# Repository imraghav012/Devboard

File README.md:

# Devboard
Custom development board made for Week 5 of Half-Life.
Made in KiCad, it uses a Raspberry Pi RP2040 on a PCB to control the other components, which can be found in this repository's Bill of Materials (BOM).
It has a USB Type-C port to supply power to and flash the board. It also includes an LDO to control voltage, a X322512MSB4SI crystal oscillator to count time, and USON-8 flash storage.
Tutorial by Kai Pereira: https://blueprint.hackclub.com/starter-projects/devboard, https://github.com/KaiPereira/build-a-devboard/tree/master

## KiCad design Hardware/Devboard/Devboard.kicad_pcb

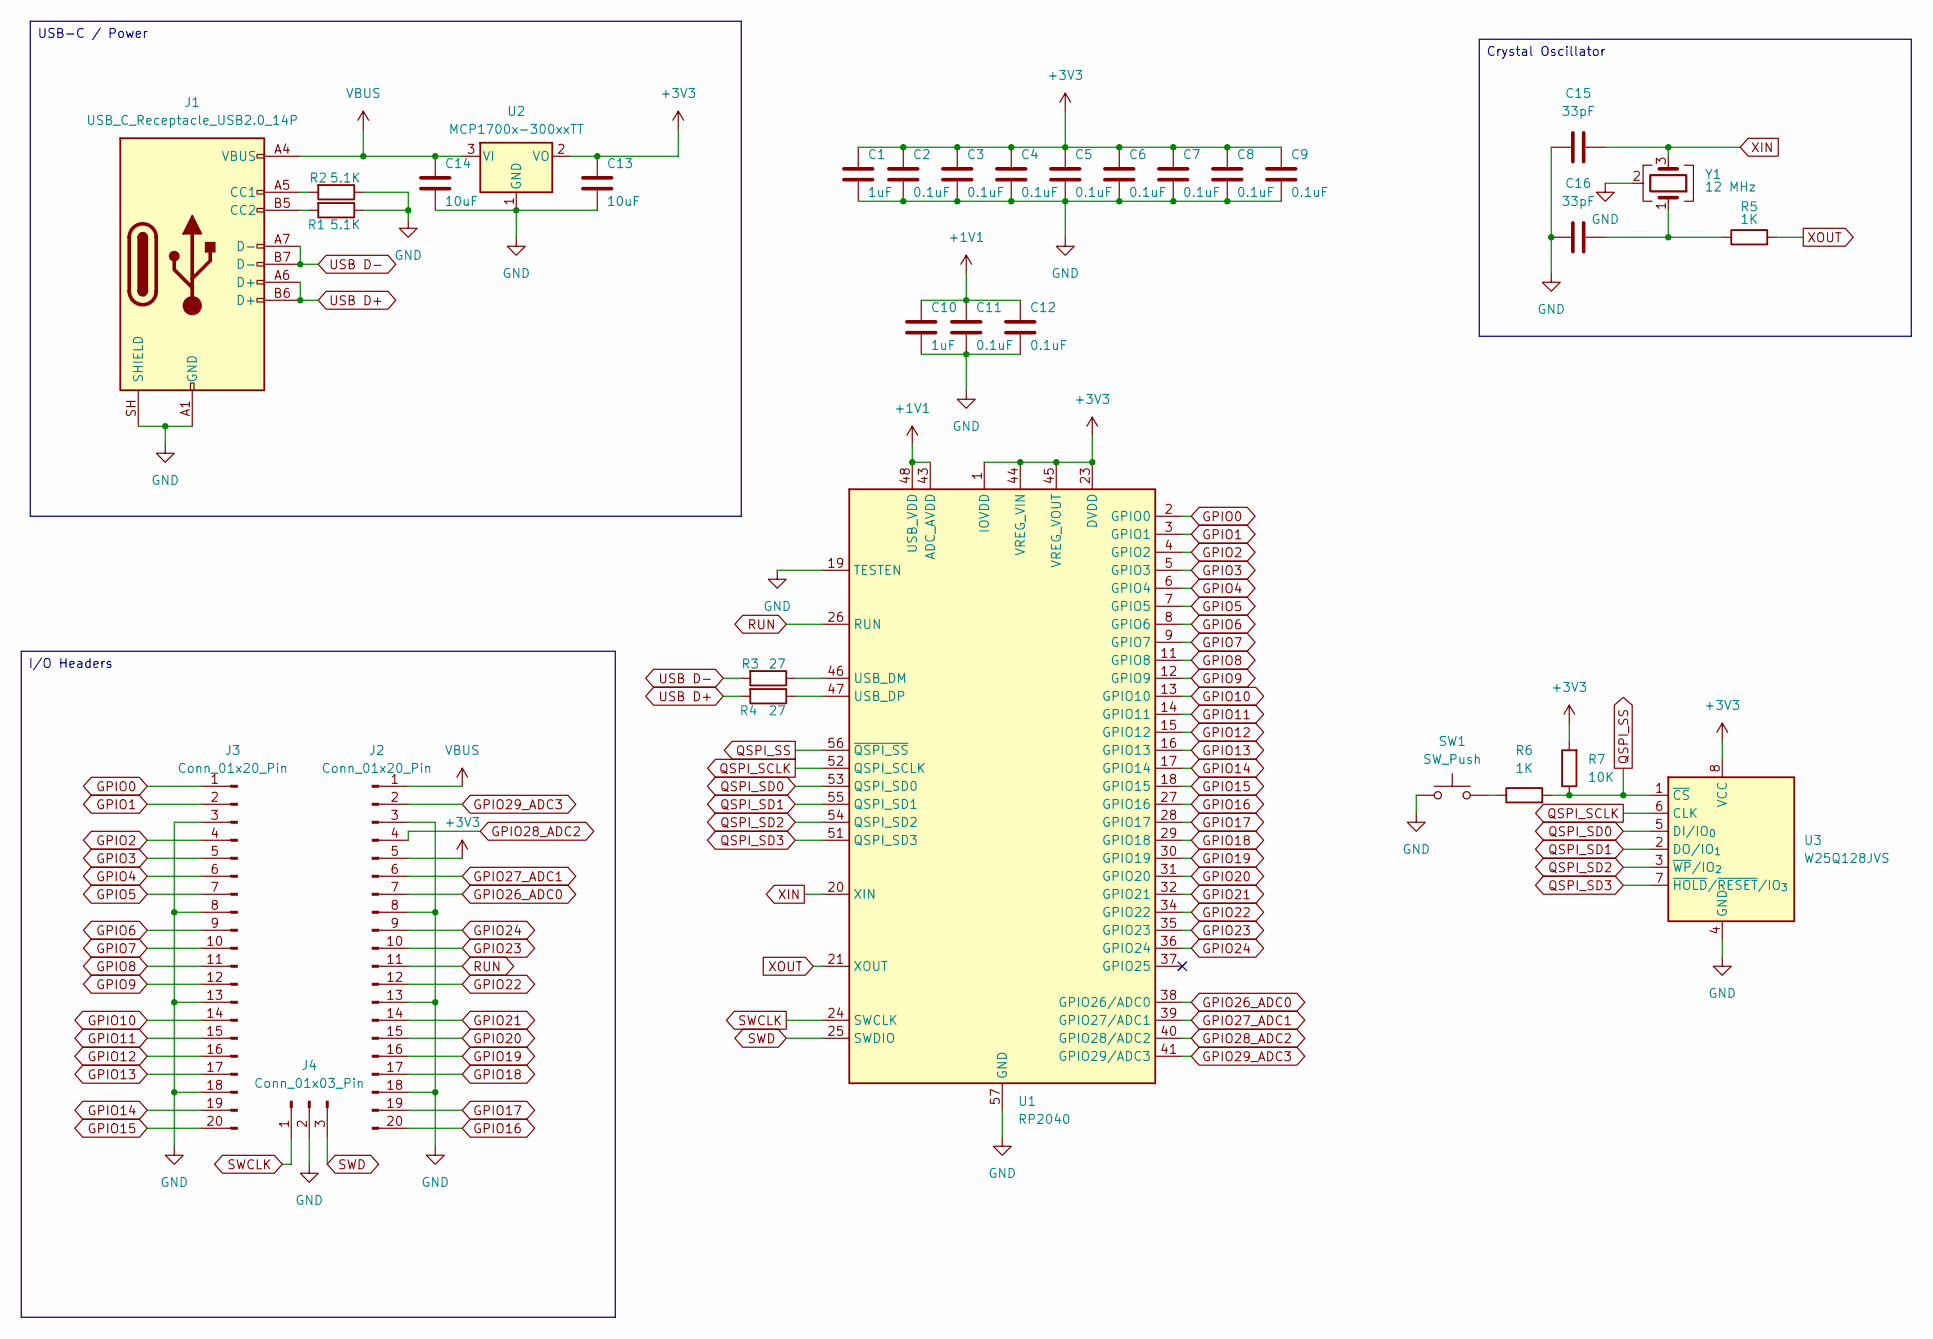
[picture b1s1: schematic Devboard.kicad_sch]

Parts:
C1, C10: 1uF; C_0402_1005Metric
C2, C3, C4, C5, C6, C7, C8, C9, C11, C12: 0.1uF; C_0402_1005Metric
C13, C14: 10uF; C_0603_1608Metric
C15, C16: 33pF; C_0402_1005Metric
J1: USB_C_Receptacle_USB2.0_14P; USB_C_Receptacle_HRO_TYPE-C-31-M-12
J2, J3: Conn_01x20_Pin; PinHeader_1x20_P2.54mm_Vertical
J4: Conn_01x03_Pin; PinHeader_1x03_P2.54mm_Vertical
R1, R2: 5.1K; R_0402_1005Metric
R3, R4: 27; R_0402_1005Metric
R5, R6: 1K; R_0402_1005Metric
R7: 10K; R_0402_1005Metric
SW1: SW_Push; SW_Push_SPST_NO_Alps_SKRK
U1: RP2040; QFN-56-1EP_7x7mm_P0.4mm_EP3.2x3.2mm
U2: MCP1700x-300xxTT; SOT-23
U3: W25Q128JVS; Winbond_USON-8-1EP_3x2mm_P0.5mm_EP0.2x1.6mm
Y1: 12 MHz; Crystal_SMD_3225-4Pin_3.2x2.5mm

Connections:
+1V1: C10.1, C11.1, C12.1, U1.43 (ADC_AVDD), U1.48 (USB_VDD)
+3V3: C1.1, C2.1, C3.1, C4.1, C5.1, C6.1, C7.1, C8.1, C9.1, C13.1, J2.5, R7.2, U1.1 (IOVDD), U1.10 (IOVDD), U1.22 (IOVDD), U1.23 (DVDD), U1.33 (IOVDD), U1.42 (IOVDD), U1.44 (VREG_VIN), U1.45 (VREG_VOUT), U1.49 (IOVDD), U1.50 (DVDD), U2.2 (VO), U3.8 (VCC)
GND: C1.2, C2.2, C3.2, C4.2, C5.2, C6.2, C7.2, C8.2, C9.2, C10.2, C11.2, C12.2, C13.2, C14.2, C15.1, C16.1, J1.A1 (GND), J1.A12 (GND), J1.B1 (GND), J1.B12 (GND), J1.SH (SHIELD), J2.3, J2.8, J2.13, J2.18, J3.3, J3.8, J3.13, J3.18, J4.2, R1.1, R2.1, SW1.1, U1.19 (TESTEN), U1.57 (GND), U2.1 (GND), U3.4 (GND), Y1.2 (G), Y1.4 (G)
GPIO0: J3.1, U1.2 (GPIO0)
GPIO1: J3.2, U1.3 (GPIO1)
GPIO2: J3.4, U1.4 (GPIO2)
GPIO3: J3.5, U1.5 (GPIO3)
GPIO4: J3.6, U1.6 (GPIO4)
GPIO5: J3.7, U1.7 (GPIO5)
GPIO6: J3.9, U1.8 (GPIO6)
GPIO7: J3.10, U1.9 (GPIO7)
GPIO8: J3.11, U1.11 (GPIO8)
GPIO9: J3.12, U1.12 (GPIO9)
GPIO10: J3.14, U1.13 (GPIO10)
GPIO11: J3.15, U1.14 (GPIO11)
GPIO12: J3.16, U1.15 (GPIO12)
GPIO13: J3.17, U1.16 (GPIO13)
GPIO14: J3.19, U1.17 (GPIO14)
GPIO15: J3.20, U1.18 (GPIO15)
GPIO16: J2.20, U1.27 (GPIO16)
GPIO17: J2.19, U1.28 (GPIO17)
GPIO18: J2.17, U1.29 (GPIO18)
GPIO19: J2.16, U1.30 (GPIO19)
GPIO20: J2.15, U1.31 (GPIO20)
GPIO21: J2.14, U1.32 (GPIO21)
GPIO22: J2.12, U1.34 (GPIO22)
GPIO23: J2.10, U1.35 (GPIO23)
GPIO24: J2.9, U1.36 (GPIO24)
GPIO26_ADC0: J2.7, U1.38 (GPIO26/ADC0)
GPIO27_ADC1: J2.6, U1.39 (GPIO27/ADC1)
GPIO28_ADC2: J2.4, U1.40 (GPIO28/ADC2)
GPIO29_ADC3: J2.2, U1.41 (GPIO29/ADC3)
unnamed: C16.2, R5.1, Y1.1
unnamed: J1.A5 (CC1), R2.2
unnamed: J1.B5 (CC2), R1.2
unnamed: R6.1, SW1.2
unnamed: R3.1, U1.46 (USB_DM)
unnamed: R4.1, U1.47 (USB_DP)
QSPI_SCLK: U1.52 (QSPI_SCLK), U3.6 (CLK)
QSPI_SD0: U1.53 (QSPI_SD0), U3.5 (DI/IO_{0})
QSPI_SD1: U1.55 (QSPI_SD1), U3.2 (DO/IO_{1})
QSPI_SD2: U1.54 (QSPI_SD2), U3.3 (~WP/IO_{2})
QSPI_SD3: U1.51 (QSPI_SD3), U3.7 (~HOLD/~RESET/IO_{3})
QSPI_SS: R6.2, R7.1, U1.56 (~QSPI_SS), U3.1 (~CS)
RUN: J2.11, U1.26 (RUN)
SWCLK: J4.1, U1.24 (SWCLK)
SWD: J4.3, U1.25 (SWDIO)
USB D+: J1.A6 (D+), J1.B6 (D+), R4.2
USB D-: J1.A7 (D-), J1.B7 (D-), R3.2
VBUS: C14.1, J1.A4 (VBUS), J1.A9 (VBUS), J1.B4 (VBUS), J1.B9 (VBUS), J2.1, U2.3 (VI)
XIN: C15.2, U1.20 (XIN), Y1.3
XOUT: R5.2, U1.21 (XOUT)

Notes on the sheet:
I/O Headers
Crystal Oscillator
USB-C / Power

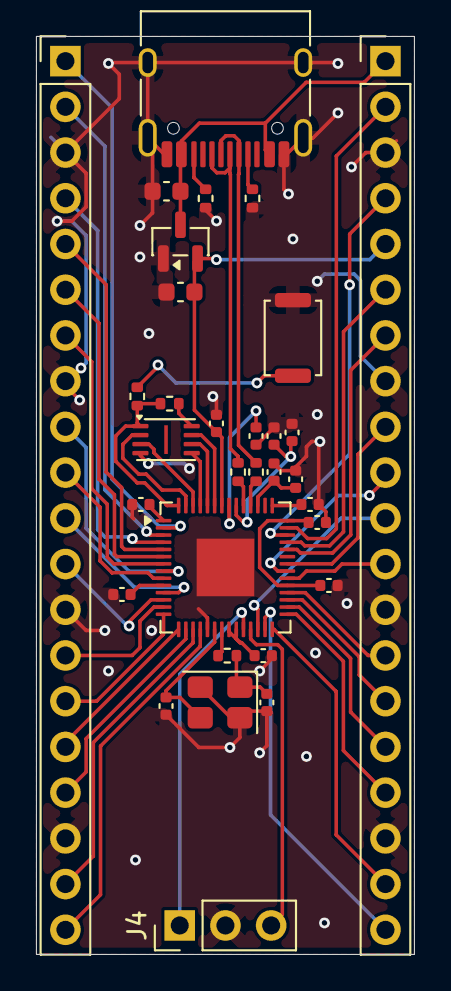
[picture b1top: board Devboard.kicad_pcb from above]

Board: 2 copper layers, 21.0 x 51.0 mm, 32 parts (0 on the bottom side), 52 nets.

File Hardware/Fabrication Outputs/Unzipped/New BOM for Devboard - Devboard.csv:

Id,Designator,Footprint,Quantity,Comment,Supplier and ref
1,"C1, C10",C_0402_1005Metric,2,1uF,
2,"C2, C3, C4, C5, C6, C7, C8, C9, C11, C12",C_0402_1005Metric,10,0.1uF,
3,"C13, C14",C_0603_1608Metric,2,10uF,
4,"C15, C16",C_0402_1005Metric,2,33pF,
5,J1,USB_C_Receptacle_HRO_TYPE-C-31-M-12,1,USB_C_Receptacle_USB2.0_14P,
6,"J2, J3",PinHeader_1x20_P2.54mm_Vertical,2,Conn_01x20_Pin,
7,J4,PinHeader_1x03_P2.54mm_Vertical,1,Conn_01x03_Pin,
8,"R1, R2",R_0402_1005Metric,2,5.1K,
9,"R3, R4",R_0402_1005Metric,2,27,
10,"R5, R6",R_0402_1005Metric,2,1K,
11,R7,R_0402_1005Metric,1,10K,
12,SW1,SW_Push_SPST_NO_Alps_SKRK,1,SW_Push,
13,U1,QFN-56-1EP_7x7mm_P0.4mm_EP3.2x3.2mm,1,RP2040,
14,U2,SOT-23,1,MCP1700x-300xxTT,
15,U3,Winbond_USON-8-1EP_3x2mm_P0.5mm_EP0.2x1.6mm,1,W25Q128JVS,
16,Y1,Crystal_SMD_3225-4Pin_3.2x2.5mm,1,12 MHz,
